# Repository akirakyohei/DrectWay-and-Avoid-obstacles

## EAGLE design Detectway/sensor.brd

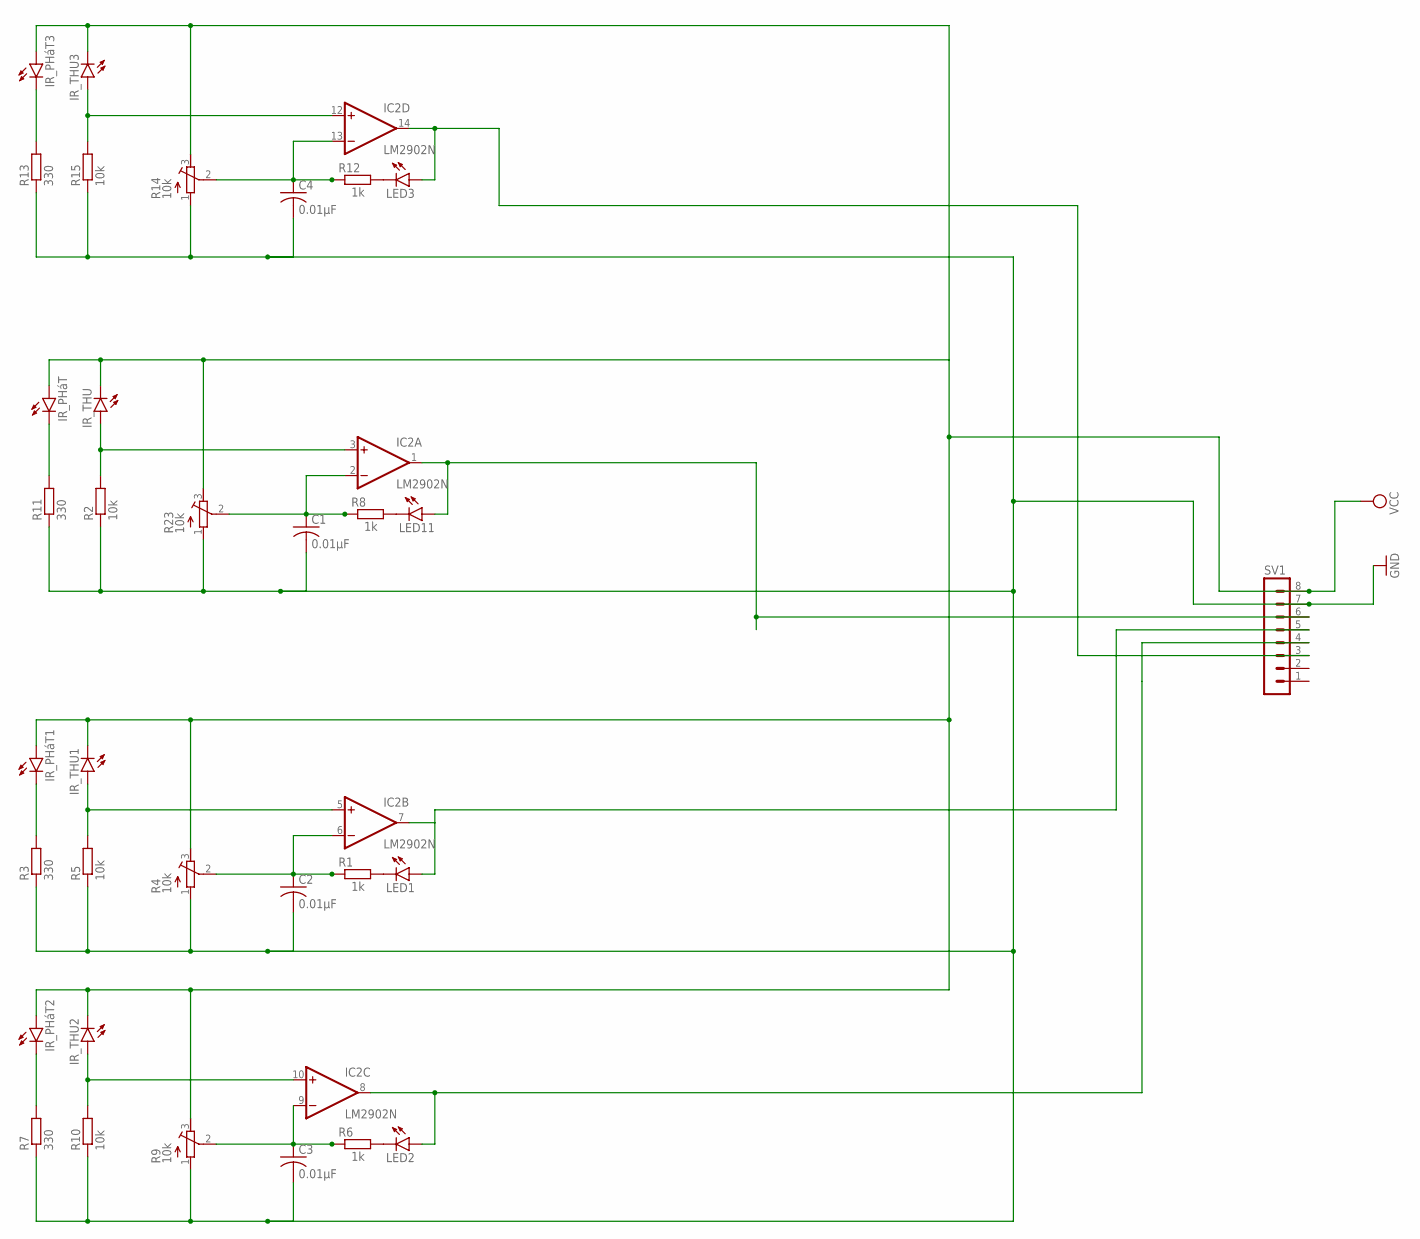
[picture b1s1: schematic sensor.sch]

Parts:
C1, C2, C3, C4: 0.01µF; C025-040X050
IC2: LM2902N; DIL14
IR_PHáT, IR_PHáT1, IR_PHáT2, IR_PHáT3: LED5MM
IR_THU, IR_THU1, IR_THU2, IR_THU3: LED5MM
LED1, LED2, LED3, LED11: LED5MM
R1, R6, R8, R12: 1k; 0204/7
R2, R5, R10, R15: 10k; 0204/7
R3, R7, R11, R13: 330; 0204/7
R4, R9, R14, R23: 10k; RTRIM3103
SV1: MA08-1W

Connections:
GND: C1.2, C2.2, C3.2, C4.2, R2.1, R3.1, R4.1 (A), R5.1, R7.1, R9.1 (A), R10.1, R11.1, R13.1, R14.1 (A), R15.1, R23.1 (A), SV1.7
unnamed: LED11.K (C), R8.2
unnamed: IC2.1 (OUT), LED11.A, SV1.6
unnamed: C1.1, IC2.2 (-IN), R8.1, R23.2 (S)
unnamed: C2.1, IC2.6 (-IN), R1.1, R4.2 (S)
unnamed: IR_PHáT.K (C), R11.2
unnamed: LED1.K (C), R1.2
unnamed: IC2.3 (+IN), IR_THU.A, R2.2
unnamed: IR_PHáT1.K (C), R3.2
unnamed: IC2.5 (+IN), IR_THU1.A, R5.2
unnamed: IC2.8 (OUT), LED2.A, SV1.4
unnamed: C3.1, IC2.9 (-IN), R6.1, R9.2 (S)
unnamed: LED2.K (C), R6.2
unnamed: IR_PHáT2.K (C), R7.2
unnamed: IC2.10 (+IN), IR_THU2.A, R10.2
unnamed: C4.1, IC2.13 (-IN), R12.1, R14.2 (S)
unnamed: LED3.K (C), R12.2
unnamed: IR_PHáT3.K (C), R13.2
unnamed: IC2.12 (+IN), IR_THU3.A, R15.2
unnamed: IC2.14 (OUT), LED3.A, SV1.3
unnamed: IC2.7 (OUT), LED1.A, SV1.5
V-: IC2.11 (V-)
VCC: IC2.4 (V+), IR_PHáT.A, IR_PHáT1.A, IR_PHáT2.A, IR_PHáT3.A, IR_THU.K (C), IR_THU1.K (C), IR_THU2.K (C), IR_THU3.K (C), R4.3 (E), R9.3 (E), R14.3 (E), R23.3 (E), SV1.8

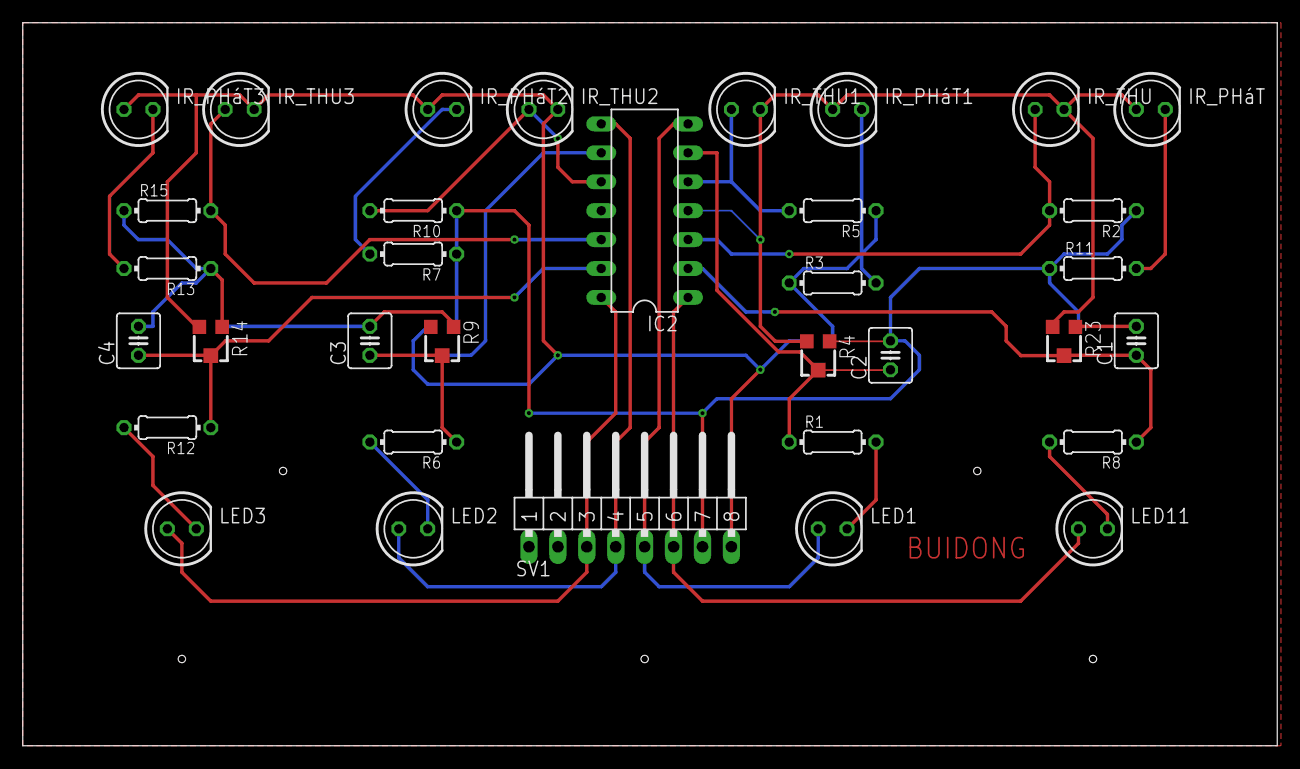
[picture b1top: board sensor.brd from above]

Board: 2 copper layers, 110.2 x 63.5 mm, 34 parts (0 on the bottom side), 22 nets.

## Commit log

2020-05-16 InitialProject
